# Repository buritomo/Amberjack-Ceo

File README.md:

# Amberjack-Ceo
 DCマウス(クラシック)開発・基板

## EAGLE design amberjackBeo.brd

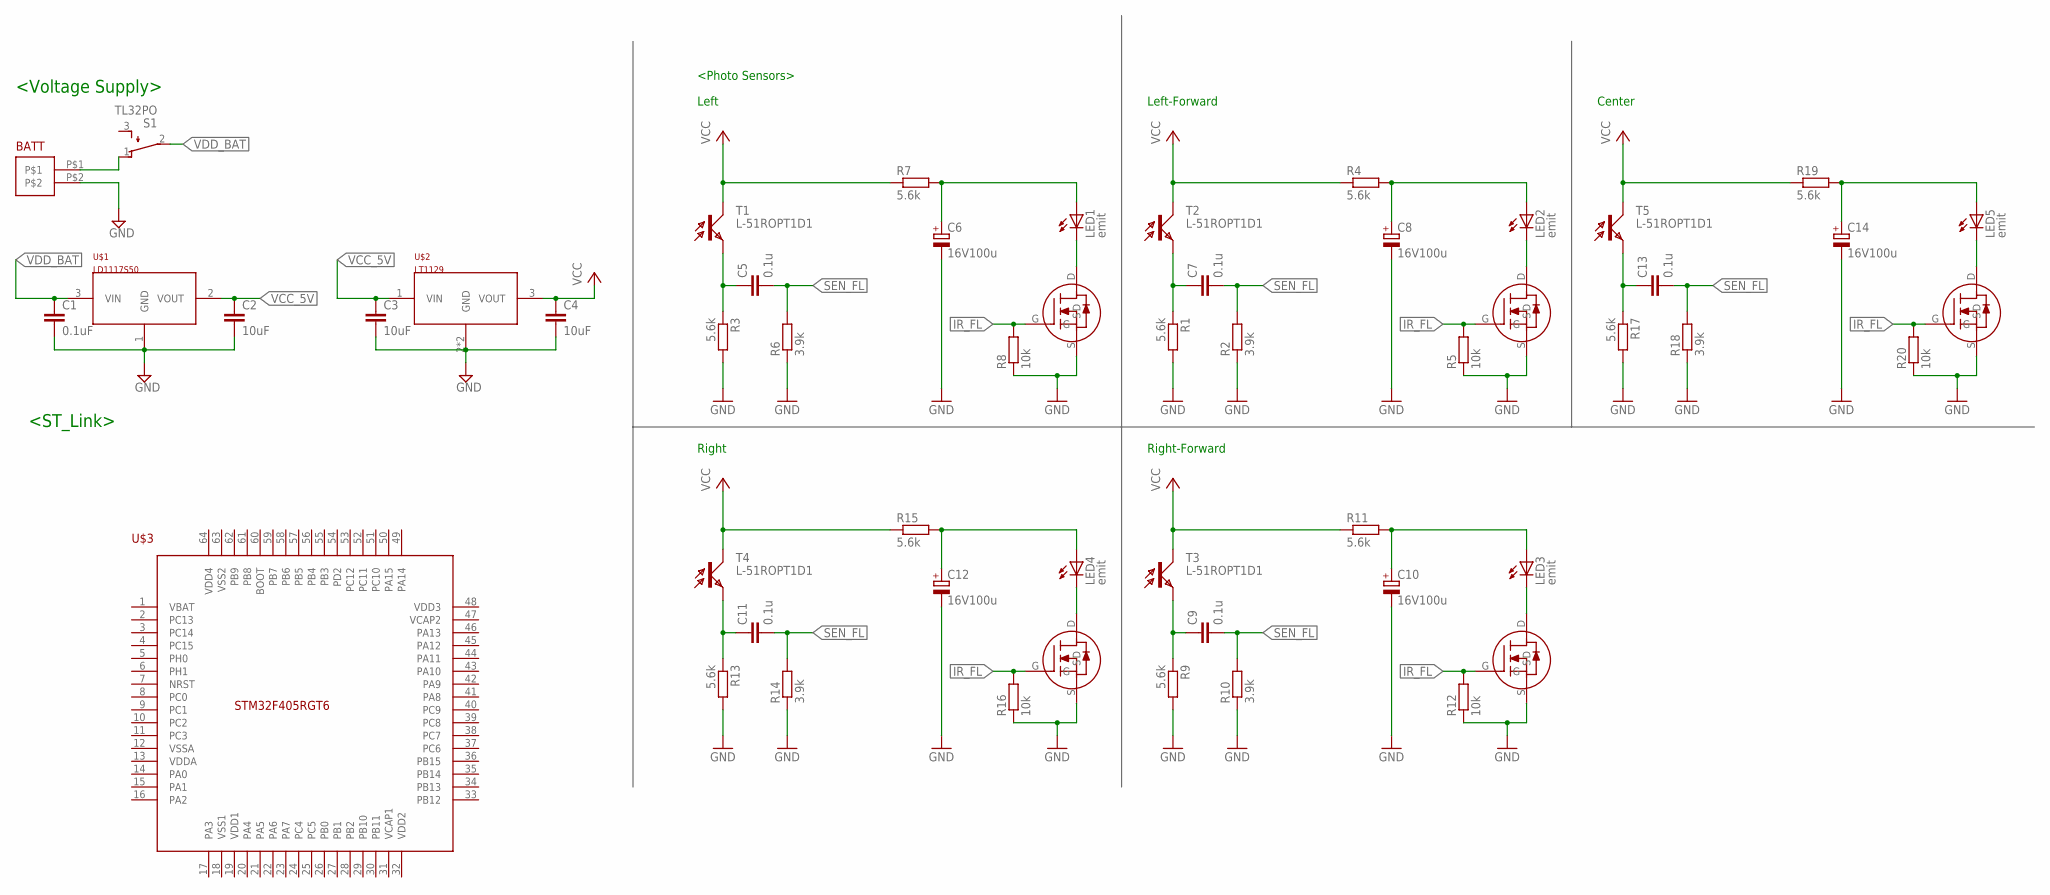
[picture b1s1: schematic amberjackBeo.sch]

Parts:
2N1, 2N2, 2N3, 2N4, 2N5: 2N7000
BATT: XA_2P
C1: 0.1uF; C0603
C2, C3, C4: 10uF; C0603
C5, C7, C9, C11, C13: 0.1u; C0805
C6, C8, C10, C12, C14: 16V100u; 153CLV-0807
LED1, LED2, LED3, LED4, LED5: emit; LED5MM
R1, R3, R4, R7, R9, R11, R13, R15, R17, R19: 5.6k; M0805
R2, R6, R10, R14, R18: 3.9k; M0805
R5, R8, R12, R16, R20: 10k; M0805
S1: TL32PO; TL3XPO
T1, T2, T3, T4, T5: L-51ROPT1D1
U$1: LD1117S50; SOT223
U$2: LT1129; SOT223
U$3: STM32F405RGT6; LQFP-ST-64-2

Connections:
GND: 2N1.S, 2N2.S, 2N3.S, 2N4.S, 2N5.S, BATT.P$2, C1.2, C2.2, C6.-, C8.-, C10.-, C12.-, C14.-, R1.2, R2.1, R3.2, R5.1, R6.1, R8.1, R9.2, R10.1, R12.1, R13.2, R14.1, R16.1, R17.2, R18.1, R20.1, U$1.1 (GND)
IR_FL: 2N1.G, 2N2.G, 2N3.G, 2N4.G, 2N5.G, R5.2, R8.2, R12.2, R16.2, R20.2
unnamed: BATT.P$1, S1.1 (O)
unnamed: C5.1, R3.1, T1.EMITTER (E)
unnamed: C6.+, LED1.A, R7.2
unnamed: C3.2, C4.2, U$2.2 (GND), U$2.4 (GND)
unnamed: 2N2.D, LED1.K (C)
unnamed: C7.1, R1.1, T2.EMITTER (E)
unnamed: C8.+, LED2.A, R4.2
unnamed: 2N1.D, LED2.K (C)
unnamed: C9.1, R9.1, T3.EMITTER (E)
unnamed: C10.+, LED3.A, R11.2
unnamed: 2N3.D, LED3.K (C)
unnamed: C11.1, R13.1, T4.EMITTER (E)
unnamed: C12.+, LED4.A, R15.2
unnamed: 2N4.D, LED4.K (C)
unnamed: C13.1, R17.1, T5.EMITTER (E)
unnamed: C14.+, LED5.A, R19.2
unnamed: 2N5.D, LED5.K (C)
SEN_FL: C5.2, C7.2, C9.2, C11.2, C13.2, R2.2, R6.2, R10.2, R14.2, R18.2
VCC: C4.1, R4.1, R7.1, R11.1, R15.1, R19.1, T1.COLLECTOR (C), T2.COLLECTOR (C), T3.COLLECTOR (C), T4.COLLECTOR (C), T5.COLLECTOR (C), U$2.3 (VOUT)
VCC_5V: C2.1, C3.1, U$1.2 (VOUT), U$2.1 (VIN)
VDD_BAT: C1.1, S1.2, U$1.3 (VIN)

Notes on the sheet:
<Voltage Supply>
<ST_Link>
<Photo Sensors>
Left
Left-Forward
Center
Right
Right-Forward

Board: 2 copper layers, 54 parts (0 on the bottom side), 23 nets, no tracks yet.
